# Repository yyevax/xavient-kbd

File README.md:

<div align="center">
    <h1>XAVIENT Keyboard</h1> 
    
    <h4>An open-sourced split ergonomic keyboard focusing on repairability and sleek thin design.</h4>
    <p><i>still a work in progress</i></p>

</div>

## Goal

The goal for this keyboard is to make a thin keyboard without sacrificing repairability or upgradablility. Taking inspiration from the Corne-ish Zen build but with hotswappable components.

## Main Features

- **User Repairable:** Controllers, Displays, and batteries are replaceable without the need of unsoldering the components.
- **Multi-Switch Compatibility:** Using Hotswappable Sockets compatible for **MX** and **Kailh LP** (*using millmax 7305 sockets*) and **Gateron LP** (*using both millmax 7305 and Gateron LP sockets*)
- **Two Layout Options:** available as a 36 key layout and a 42 key layout (52 key layout on-going development)
- **Large Battery Capacity** 2 allocated battery slots with each slot having  a 250mah maximum battery capacity
- **Thin Profile:** Achieved a 8mm thick keyboard by having a sandwiched layout for the controller and display.
- **Upgradability:** Future expansion to a Trackpoint [WIP] (will take up one battery slot)

## Versions
**[Version 1](https://github.com/yyevax/xavient-kbd)** *Tested.* My Current build, This uses a combination of gateron low profile sockets and millmax sockets (for choc and high profile). 

**[Version 2](https://github.com/yyevax/xavient-kbd/tree/version_2)** *Untested.* Proceed at your own risk although feedback is highly encouraged. This uses gateron hotswap and choc hotswap sockets.

**[Version 3](https://github.com/yyevax/xavient-kbd/tree/with_trackpoint)** *Under Develompent.* No updates as of yet. But planning on building this keyboard further to support a trackpoint.

## Keyboard Layout Comparisons
The placement of the keys for this keyboard are loosely based on both the Crkbd (Corne) and Swoop Keyboards. The crkbd keyboard is one of the most popular keyboards in the space hence the layout for the microcontroller for this keyboard followes the one design in the Corne Keyboard for easier compatibility of existing softwares. The swoop keyboard was my introduction to the split mechanical keyboards which lead me to making various keyboard such as this. 

## The Whys and Hows

### Repairability

During various iterations at building a keyboard the first things that I encountered various issues that led me building this keyboard. One of those things were with regards to the controller layout. The usual route was to have the Pro-Micro/NiceNano be mounted on [Mill Max Low Profile Sockets](https://splitkb.com/products/mill-max-low-profile-sockets?srsltid=AfmBOorAvRTDPpa_qCGRBX-qHv9DB7s7FVfZZd7idIL-V0db0YljPTJA) or straight to surface mounted PCBs.

- **Mill Max Low Profile Sockets:** This allows the battery to be sandwiched between the PCB and the Microcontroller. Add the display on top of the microcontroller and you have a thick stack of components.
  - *Repairability*: 5/5 - easily hotswap components.
  - *Looks*: 2/5 - open case design which is cheaper (prefer an enclosed case).
  - *Complexity*: 2/5 - beginner/budget friendly.
  - *Modularity*: 5/5 - option to convert builds from wired to wireless.
    Some examples of this are the Swoop Keyboard, Corne v4, and various other open-sourced keyboards.
- **Surface-mounted PCB:** This allows the pcb to be thin but will require a dedicated case and different pcb designs for wired and wireless builds.
  - *Repairability*: 1/5 - components are tiny and hard to hand solder.
  - *Looks*: 4/5 - often designed to have an enclosed case.
  - *Complexity*: 2/5 - not beginner/budget friendly due to the complexity.
  - *Modularity*: 1/5 - separate builds for wired and wireless.
    Some examples of this are the Corne-ish Zen Keyboard, Corne KBD (main branch), Seeed Xiao-based keyboards and various other keyboards from various sellers.

Xavient tries to combine the best features of both worlds into one. The solution is to use 7305  Millmax Sockets not just for key switches but for the controller and display as well. This saves space height-wise and adds a better space for bigger batteries. 

### Multi-Switch Compatibility
There are a lot of mechanical switches in the space and choosing one sometimes is a daunting task. During my experimentation, I locked myself into soldering key switches. This effectively removed the option to try other switches and is a nightmare to repair. Having the option of what key switches to use is a pesonal preference and gives you an opportunity to explore various switches at little to no time.

A dedicated switch plate is required as an additional part when using the keyboard with MX switches. This is done to provide stability to the switches. Both MX switches and Choc switches require Mill-Max Sockets. While Gateron LP switches have the option of using Mill-Max Sockets or the Gateron LP sockets.

For more switch options in the future, build the keyboard with B, C, and D layouts.

### Long Battery Life
While the case is designed to be thin, it does not compromise battery capacity. Each half can accommodate upto 250 mah batteries for longer runtime. There is also an option for a 2 battery slot in each , this utilizes the slot intended for a trackpoint.

### Thin Profile
This keyboard is around **8mm** (*body only*) thin without having a lot of compromises. This means having displays, larger batteries, and hotswappable components. This is achieved by having the microcontroller and displays as close as possible to the pcb with out soldering which in turn makes it modular.

Various keyboard uses Mill Max Low Profile Sockets for the controller. The layers are composed of the pcb, sockets and battery, microcontroller, and oled display. This stack of components (includes acrylic casing) while modular is around 15 mm in height. Add in an acrylic cover on top and it would add another 1.5 mm.

Instead of pins or directly soldering the microcontroller, mill max sockets intended for key switches were utilized for the microcontrollers and displays. This way, the components are as close to the pcb without being soldered. 

Having the pcb sandwiched in between the display and microcontroller achieves around 6mm in thickness.

### Compromises
While the goal of 8mm thick modular build was achieved, it is not without its compromises.

**PCB Layout:** To achieve the sandwiched layout, it sacrifices the reversable PCB layout that some custom keyboards have.

**Battery Placement:** With the space in between the PCB and microcontroller gone, a dedicated space was needed for the battery. This was also a blessing in disguise since it allowed bigger battery capacity which provides longer runtime.

**Dedicated Case:** Due to the tight constraints of this build, a dedicated case is required for this layout to work.

### Future Implementations
**PCB Development:** The current pcb was developed for the possibility of adding a trackpoint, hence it requires some of the keys to use mill max sockets. The use of mill-max sockets also allowed the pcb to be complatible for MX, and LP switches from Gateron to Kailh. However, having the full flexibility being able to swap from various switches will add to the cost of the build significantly. A new board will be designed to address this issue. It will have Hot-swap sockets for both kailh low profile and MX switches. Gateron LP v3 are compatible with MX switch pin layout hence will reduce the cost further but with the same implementation. (This will lose the trackpoint functionality.)

**Seeed Xiao Build:** The current keyboard layout uses the Nice!NanoV2/ProMicro microcontroller layout. The Seeed Xiao is one of the famous microcontrollers in the keyboard space that is in the middle of the nice!nanov2 and its clones price-wise. It will need some more time to build this keyboard with the same philisophy of the current build. Thin. Modular. Repairable. (This will lose the trackpoing functionality.)

**Pointing Devices:** There are already implementations for pointing devices in various zmk keyboards, but these still remain experimental at this time, however the pcb already has a provision for a trackpoint. 

Other pointing devices such as trackballs and trackpads will still need more time to develop.

**Case Alternatives:** The current case uses heat set inserts which provides a clean look on the top of the keyboard. The usual route is to have the case and pcb sandwiched by 2 screws and a brass threaded pillar. Acrylic cases can also be designed as an alternative, will require further testing.

**Unibody Keyboard:** This will provide another layout for users to choose from. 

## Notes

**[Wired Build:](https://github.com/duanexavierbondad/xavient-kbd/tree/main/pcb/Wired)** This is still under development and untested. Proceed at your own risk.

**[Software:](https://github.com/duanexavierbondad/zmk-config-xavien/tree/stable/xavient)** The software for this keyboard is available. Is uses colemak-dh on a 36/42 key layout. You can find the 32 Key config files [here](https://github.com/yyevax/zmk-config-xavien/tree/stable/xavient) and the 42 Key config [here](https://github.com/yyevax/zmk-config-xavient/tree/stable/xavient3x6). You can also opt for the build with ZMK Studio [here](https://github.com/duanexavierbondad/zmk-config-xavien/tree/stable/xavient_zmk-studio).

## Credits
This keyboard build followed some inspirations on various open-sourced keyboards listed below:

- [Corne](https://github.com/foostan/crkbd): basing the footprint of the controller here since this is the most common keyboard.
- [Swoop](https://github.com/jimmerricks/swoop): used as my first keyboard when I was exploring the world of split-keyboards
- [Flake](https://github.com/anywhy-io/flake): got some inspiration on how to implement jst battery connections and MX switches mounting.
- [TPS42](https://github.com/crehmann/TPS42): basis for the trackpoint routing and mounting.

Some Close-sourced keyboards:

- [Sweet-Corne](https://imgur.com/a/sweep-corne-gjZDgmk): My first attempt at building a keyboard from scratch. (Lost Files)
- [Corne-ish Zen](https://lowprokb.ca/products/corne-ish-zen): A thin split keyboard with e-ink displays. (Sold Out)

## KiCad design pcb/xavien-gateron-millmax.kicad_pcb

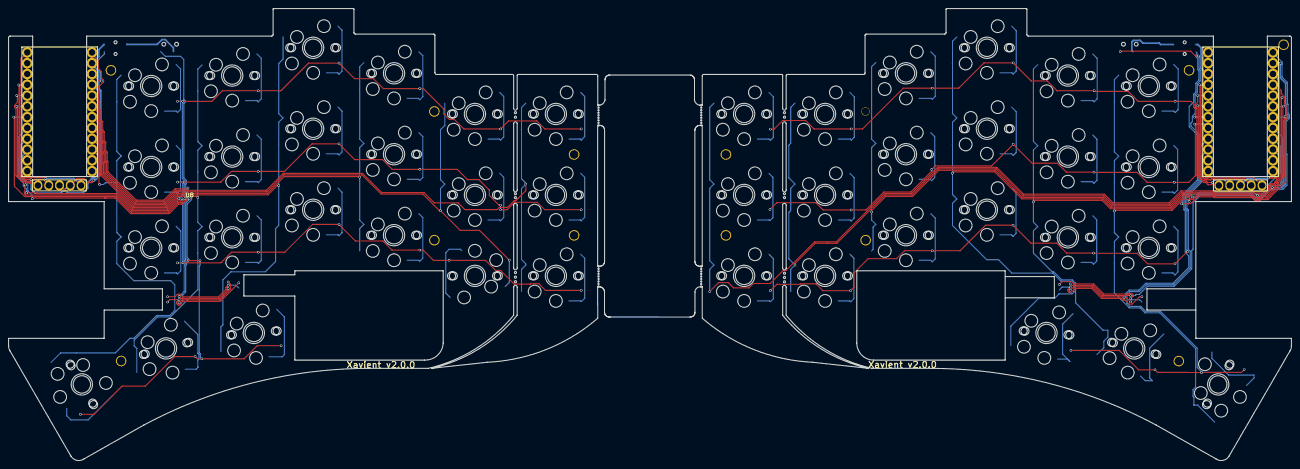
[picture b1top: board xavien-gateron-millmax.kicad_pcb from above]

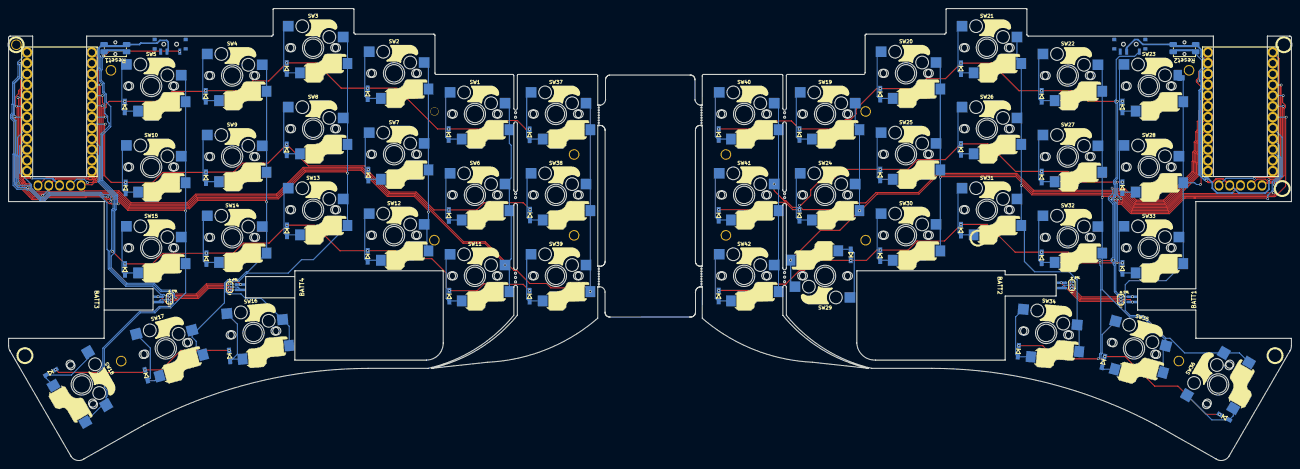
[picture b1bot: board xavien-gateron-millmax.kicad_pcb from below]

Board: 2 copper layers, 301.9 x 106.3 mm, 130 parts (10 on the bottom side), 82 nets.

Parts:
BATT1, BATT2, BATT3, BATT4: Battery; JST_1.25mm_mid-mount
BT8, BT9, BT24, BT25: Breakaway Tabs; Breakaway_Tabs
BT10, BT11, BT12, BT13, BT14, BT15, BT16, BT26, BT27, BT28, BT29, BT30, BT31, BT32: Breakaway Tabs; Breakaway_0.5mm
D1, D2, D3, D4, D5, D6, D7, D8, D9, D10, D11, D12, D13, D14, D15, D16, D17, D18, D19, D20, D21, D22, D23, D24, D25, D26, D27, D28, D29, D30, D31, D32, D33, D34, D35, D36, D37, D38, D39, D40, D41, D42: 1N4148W; D_SMD_back
Display1, Display2: nice!view; niceview_rev
JP1, JP2, JP3, JP4: Jumper_3P; SolderJumper-3_P
L1, L12, L13: Hole
L6, L7: Hole; HOLE_M2_TH
PSW1, PSW2: Power; PowerB.CU
R4, R5, R7: Hole; HOLE_M2_TH
R6, R12: Hole
R13: (no value)
Reset1, Reset2: SW_PUSH1; TS-1289VE-4
SW1, SW2, SW3, SW4, SW5, SW6, SW7, SW8, SW9, SW10, SW11, SW12, SW13, SW14, SW15, SW16, SW17, SW18, SW19, SW20, SW21, SW22, SW23, SW24, SW25, SW26, SW27, SW28, SW29, SW30, SW31, SW32, SW33, SW34, SW35, SW36, SW37, SW38, SW39, SW40, SW41, SW42: SW_PUSH; keyswitch_cherrymx_hotswap_1u
U1, U2: ProMicro; ProMicro_millmax
U8: Hole; TPSensorModule

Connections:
GND: Display1.4 (GND), PSW2.2 (B), Reset1.2, U2.3 (GND), U2.4 (GND), U2.23 (GND)
GND_A: Display2.4 (GND), PSW1.2 (B), Reset2.2, U1.3 (GND), U1.4 (GND), U1.23 (GND)
unnamed: BATT1.1 (+), BATT2.1 (+), JP1.2 (C)
unnamed: BATT1.2 (-), BATT2.2 (-), JP2.2 (C)
unnamed: BATT3.1 (+), BATT4.1 (+), JP3.2 (C)
unnamed: BATT3.2 (-), BATT4.2 (-), JP4.2 (C)
unnamed: D1.2 (A), SW1.2
unnamed: D2.2 (A), SW2.2
unnamed: D3.2 (A), SW3.2
unnamed: D4.2 (A), SW4.2
unnamed: D5.2 (A), SW5.2
unnamed: D6.2 (A), SW6.2
unnamed: D7.2 (A), SW7.2
unnamed: D8.2 (A), SW8.2
unnamed: D9.2 (A), SW9.2
unnamed: D10.2 (A), SW10.2
unnamed: D11.2 (A), SW11.2
unnamed: D12.2 (A), SW12.2
unnamed: D13.2 (A), SW13.2
unnamed: D14.2 (A), SW14.2
unnamed: D15.2 (A), SW15.2
unnamed: D16.2 (A), SW16.2
unnamed: D17.2 (A), SW17.2
unnamed: D18.2 (A), SW18.2
unnamed: D19.2 (A), SW19.2
unnamed: D20.2 (A), SW20.2
unnamed: D21.2 (A), SW21.2
unnamed: D22.2 (A), SW22.2
unnamed: D23.2 (A), SW23.2
unnamed: D24.2 (A), SW24.2
unnamed: D25.2 (A), SW25.2
unnamed: D26.2 (A), SW26.2
unnamed: D27.2 (A), SW27.2
unnamed: D28.2 (A), SW28.2
unnamed: D29.2 (A), SW29.2
unnamed: D30.2 (A), SW30.2
unnamed: D31.2 (A), SW31.2
unnamed: D32.2 (A), SW32.2
unnamed: D33.2 (A), SW33.2
unnamed: D34.2 (A), SW34.2
unnamed: D35.2 (A), SW35.2
unnamed: D36.2 (A), SW36.2
unnamed: D37.2 (A), SW37.2
unnamed: D38.2 (A), SW38.2
unnamed: D39.2 (A), SW39.2
unnamed: D40.2 (A), SW40.2
unnamed: D41.2 (A), SW41.2
unnamed: D42.2 (A), SW42.2
unnamed: JP1.1 (A), JP2.3 (B), PSW1.1 (A)
unnamed: JP3.1 (A), JP4.1 (A), PSW2.1 (A)
VCC: Display1.3 (VCC), U2.21 (VCC)
VDD: Display2.3 (VCC), U1.21 (VCC)
col0: SW37.1, SW38.1, SW39.1, U2.20 (F4)
col0_r: SW40.1, SW41.1, SW42.1, U1.20 (F4)
col1: SW1.1, SW6.1, SW11.1, U2.19 (F5)
col1_r: SW19.1, SW24.1, SW29.1, U1.19 (F5)
col2: SW2.1, SW7.1, SW12.1, U2.18 (F6)
col2_r: SW20.1, SW25.1, SW30.1, U1.18 (F6)
col3: SW3.1, SW8.1, SW13.1, SW16.1, U2.17 (F7)
col3_r: SW21.1, SW26.1, SW31.1, SW34.1, U1.17 (F7)
col4: SW4.1, SW9.1, SW14.1, SW17.1, U2.16 (B1)
col4_r: SW22.1, SW27.1, SW32.1, SW35.1, U1.16 (B1)
col5: SW5.1, SW10.1, SW15.1, SW18.1, U2.15 (B3)
col5_r: SW23.1, SW28.1, SW33.1, SW36.1, U1.15 (B3)
cs: Display1.5 (CS), U2.1 (TX)
cs_r: Display2.5 (CS), U1.1 (TX)
mosi: Display1.1 (MOSI), U2.5 (SDA)
mosi_r: Display2.1 (MOSI), U1.5 (SDA)
raw: JP3.3 (B), JP4.3 (B), U2.24 (RAW)
raw_r: JP1.3 (B), JP2.1 (A), U1.24 (RAW)
reset: Reset1.1, U2.22 (RST)
reset_r: Reset2.1, U1.22 (RST)
row0: D1.1 (K), D2.1 (K), D3.1 (K), D4.1 (K), D5.1 (K), D37.1 (K), U2.7 (D4)
row0_r: D19.1 (K), D20.1 (K), D21.1 (K), D22.1 (K), D23.1 (K), D40.1 (K), U1.7 (D4)
row1: D6.1 (K), D7.1 (K), D8.1 (K), D9.1 (K), D10.1 (K), D38.1 (K), U2.8 (C6)
row1_r: D24.1 (K), D25.1 (K), D26.1 (K), D27.1 (K), D28.1 (K), D41.1 (K), U1.8 (C6)
row2: D11.1 (K), D12.1 (K), D13.1 (K), D14.1 (K), D15.1 (K), D39.1 (K), U2.9 (D7)
row2_r: D29.1 (K), D30.1 (K), D31.1 (K), D32.1 (K), D33.1 (K), D42.1 (K), U1.9 (D7)
row3: D16.1 (K), D17.1 (K), D18.1 (K), U2.10 (E6)
row3_r: D34.1 (K), D35.1 (K), D36.1 (K), U1.10 (E6)
sck: Display1.2 (SCK), U2.6 (SCL)
sck_r: Display2.2 (SCK), U1.6 (SCL)

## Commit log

2025-03-31 Create LICENSE_CC
2025-03-31 Rename LICENSE to LICENSE_MIT
2025-03-31 xavient repo | v1
2025-03-31 xavient repo | v1.0.1
2025-03-31 xavient repo | v1.0.2
2025-03-31 Rename xavient-build.JPG to xavient-build.jpg
2025-03-31 xavient repo | v1.0.3
2025-03-31 build guide v1.0.1
2025-09-25 xavient documentation v2
2025-10-02 added image for keyboard layouts
2025-10-02 added information on readme
2025-10-02 updated cross section image
2025-10-02 v1.0.0 | xavient documentation
2025-10-02 v1.0.1 | fix 3d cases
2025-10-03 v1.0.2 | added gerber files and started build guide
2025-10-03 v1.0.3 | build guide
2025-10-07 v 1.0.4 | updated readme
2026-01-22 v1.0.4 | case files cleanup
2026-04-27 added config files for 32 and 42 key layouts
2026-04-27 added pcb version 2
